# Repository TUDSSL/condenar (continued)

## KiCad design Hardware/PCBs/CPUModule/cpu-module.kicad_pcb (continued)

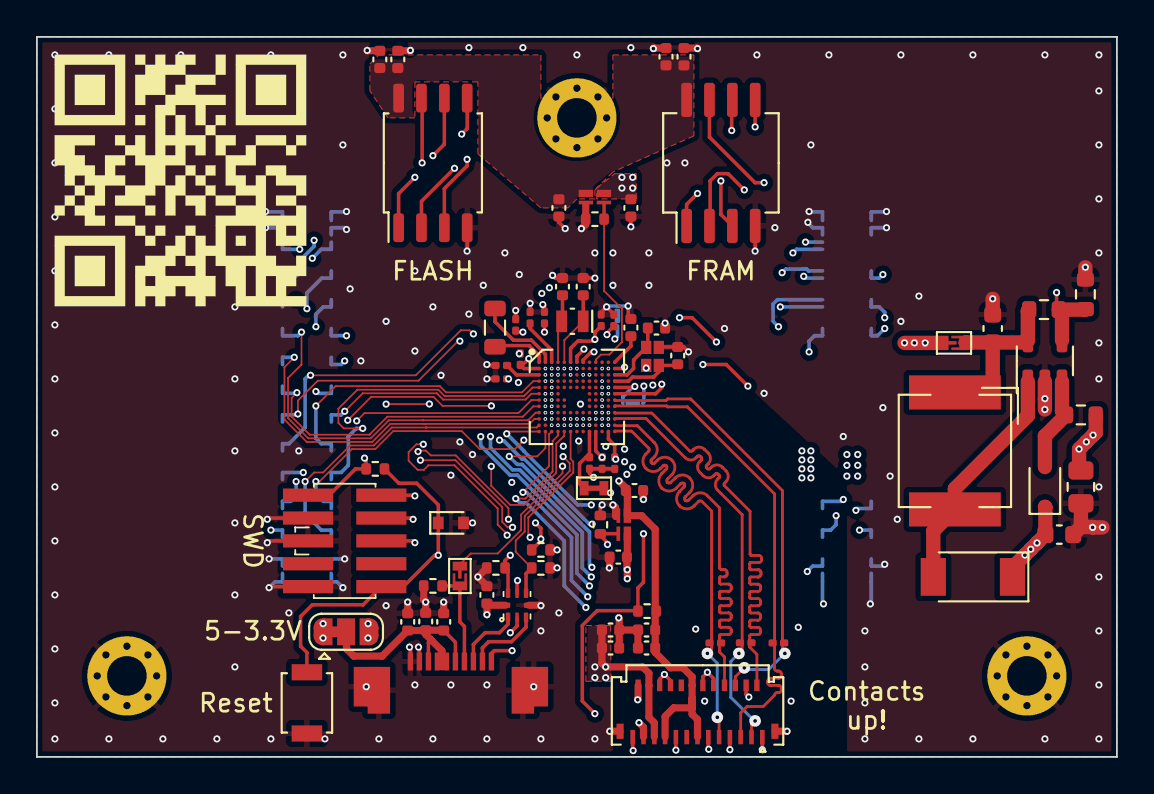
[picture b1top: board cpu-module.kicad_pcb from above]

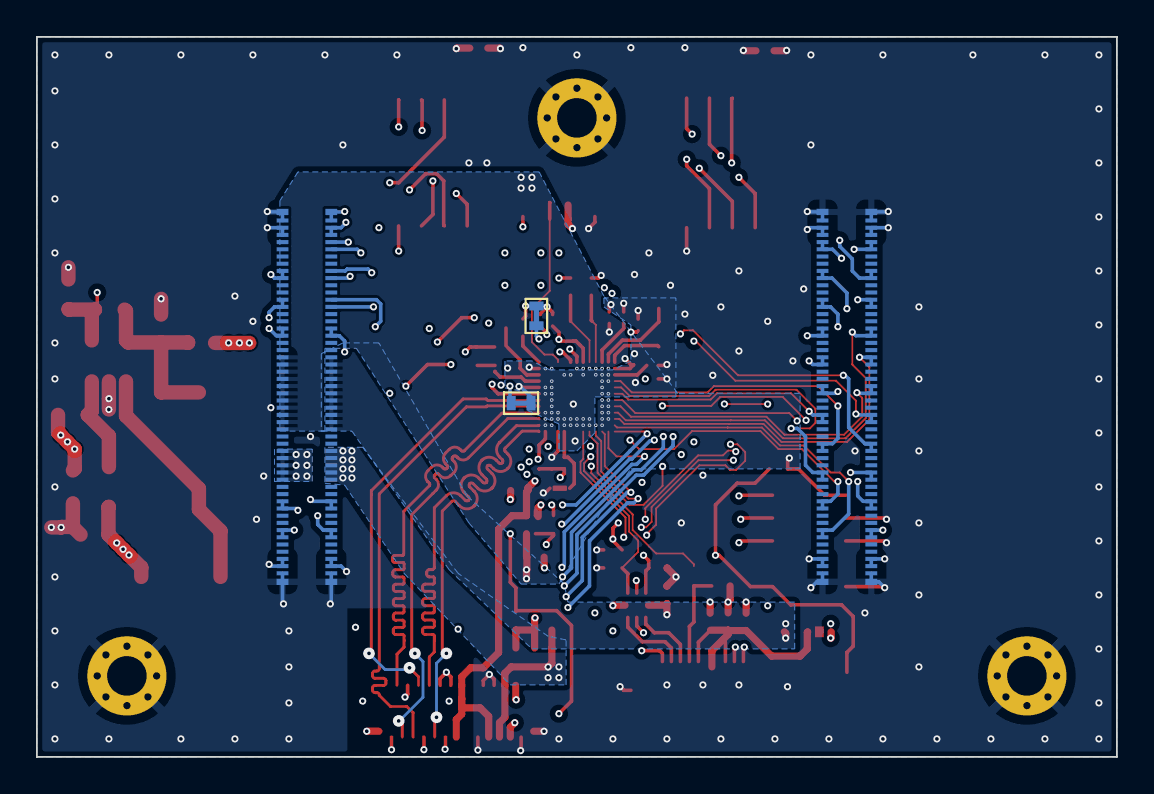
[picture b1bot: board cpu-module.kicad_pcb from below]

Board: 4 copper layers, 60.0 x 40.0 mm, 80 parts (4 on the bottom side), 98 nets.

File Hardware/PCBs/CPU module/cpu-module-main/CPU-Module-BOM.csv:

Item,Qty,Reference(s),Value,LibPart,Footprint,Datasheet,MPN
1,2,"C1, C3",6pF,Device:C,Capacitor_SMD:C_0402_1005Metric,~,CC0402BRNPO9BN6R0
2,6,"C2, C12, C13, C14, C15, C16",2.2 uF,Device:C,Capacitor_SMD:C_0201_0603Metric,~,GRM033R61A225KE47D
3,7,"C4, C18, C19, C23, C29, C32, C33",100nF,Device:C,Capacitor_SMD:C_0402_1005Metric,~,GRM155R71C104KA88J
4,2,"C5, C8",4pF DNP,Device:C,Capacitor_SMD:C_0402_1005Metric,~,CQ0402ARNPO9BN4R0
5,4,"C6, C7, C9, C10",1uF,Device:C,Capacitor_SMD:C_0201_0603Metric,~,GRM033C81A105ME05D
6,1,C11,4.7nF,Device:C,Capacitor_SMD:C_0201_0603Metric,~,GRM033R61E472KA12D
7,9,"C17, C21, C22, C26, C27, C28, C30, C31, C34",1uF,Device:C,Capacitor_SMD:C_0402_1005Metric,~,CL05A105KP5NNNC
8,1,C20,10uF,Device:C,Capacitor_SMD:C_0603_1608Metric,~,GRT188R61C106KE13D
9,1,C24,2.2uF,Device:C,Capacitor_SMD:C_0603_1608Metric,~,GRM188R61H225KE11D
10,1,C25,10uF,Device:C,Capacitor_SMD:C_0402_1005Metric,~,CL05A106MP8NUB8
11,1,D1,ESD,Device:D_Zener,Diode_SMD:D_SOD-523,~,PESD5V0X1UB
12,1,D2,"PMEG4050EP,115",Device:D_Schottky_Filled,Diode_SMD:D_SOD-128,~,"PMEG4050EP,115"
13,1,D3,"BZX84J-C20,115",Device:D_Schottky_Filled,Diode_SMD:D_SOD-323F,~,"BZX84J-C20,115"
14,1,J1,SWD_10,jaspers_lib:SWD_10,jaspers_footprints:ftsh-105-01-f-dv-k,http://infocenter.arm.com/help/topic/com.arm.doc.ddi0314h/DD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,ftsh-105-01-f-dv-k
15,1,J3,52745-1097,jaspers_lib:52745-1097,jaspers_footprints:FPC_10_TOP,~,52745-1097
16,1,J8,FH35C-25S-0.3SHW(50),Connector_Generic_MountingPin:Conn_01x25_MountingPin,jaspers_footprints:FH35C-25S-0.3SHW_2Rows-27Pins-1MP_P0.60mm_Horizontal,~,FH35C-25S-0.3SHW(50)
17,2,"J10, J11",DF40C-100DP-0-4V,jaspers_lib:DF40C-100DP-0-4V,jaspers_footprints:DF40C-100DP,~,DF40C-100DP-0-4V
18,1,L1,2.2 uH,Device:L,Inductor_SMD:L_0805_2012Metric,~,DFE201210U-2R2M=P2
19,1,L2,LQH3NPH150MMEL,Device:L,jaspers_footprints:VLS6045EX,~,LQH3NPH150MMEL
20,3,"R1, R5, R14",100k,Device:R,Resistor_SMD:R_0402_1005Metric,~,ERJ-2RKF1003X
21,3,"R2, R3, R4",100 DNP,Device:R,Resistor_SMD:R_0201_0603Metric,~,CRCW0201100RFNED
22,1,R6,0,Device:R,Resistor_SMD:R_0402_1005Metric,~,ERJ-2GE0R00X
23,1,R7,DNP,Device:R,Resistor_SMD:R_0603_1608Metric,~,
24,4,"R8, R9, R10, R15",10M,Device:R,Resistor_SMD:R_0402_1005Metric,~,RC0402FR-0710ML
25,1,R11,100k,Device:R,Resistor_SMD:R_0603_1608Metric,~,ERJ-3EKF1003V
26,1,R12,100,Device:R,Resistor_SMD:R_0603_1608Metric,~,CRCW0603100RFKEAHP
27,1,R13,ERJP06F10R0V,Device:R,Resistor_SMD:R_0805_2012Metric,~,ERJP06F10R0V
28,1,SW1,SW_Push,Switch:SW_Push,Button_Switch_SMD:SW_SPST_B3U-1000P,~,B3U-1000P
29,1,U1,Apollo_4,jaspers_lib:Apollo_4,jaspers_footprints:Apollo4-BGA-156_13x12_5.0x5.0mm,,Apollo 4
30,2,"U2, U7",SLG5NT1593V,jaspers_lib:SLG5NT1593V,jaspers_footprints:SLG5NT1593V,https://www.mouser.com/datasheet/2/665/silego_04052017_SLG5N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,SLG5NT1593V
31,1,U3,SN74AUP3G34RSE,jaspers_lib:SN74AUP3G34RSE,jaspers_footprints:Texas_RSE_8_UQFN,https://www.ti.com/lit/ds/symlink/sn74aup3g34.pdf,SN74AUP3G34RSE
32,1,U4,LM3410XMF,jaspers_lib:LM3410XMF,Package_TO_SOT_SMD:SOT-23-5,https://www.ti.com/lit/ds/symlink/lm3410.pdf,LM3410XMF
33,1,U5,MX25R6435FM2IH0,jaspers_lib:MX25R6435FM2IH0,Package_SO:SOP-8_5.28x5.23mm_P1.27mm,https://www.farnell.com/datasheets/2815329.pdf,MX25R6435FM2IH0
34,1,U6,MB85RS4MT,jaspers_lib:MB85RS4MT,Package_SO:SO-8_5.3x6.2mm_P1.27mm,https://www.fujitsu.com/global/documents/products/devices/se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,MB85RS4MT
35,1,Y1,32.768Hz,Device:Crystal,Crystal:Crystal_SMD_MicroCrystal_CM9V-T1A-2Pin_1.6x1.0mm,http://www.txccrystal.com/images/pdf/9ht12.pdf,9HT12-32.768KDZY
36,1,Y2,ABM12W-32.0000MHZ,jaspers_lib:ABM12W-32.0000MHZ,jaspers_footprints:Crystal_SMD_Abracon_ABM12B-4Pin_1.6x1.2mm,https://abracon.com/Resonators/ABM12W.pdf,ABM12W-32.0000MHZ-6-D1X-T3

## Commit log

2023-09-01 folder structure created
2023-09-01 cleaning of DS_Store
2023-09-01 removal of remaining .DS_Store files
2023-09-01 readme files added
2023-09-01 new readme files added
2023-09-01 preliminary studies files added
2023-09-03 Preliminary study software and paths shortened
2023-09-03 Enclosure and more paths shortened
2023-09-03 Hardware files
2023-09-03 Update gitignore
2023-09-03 Menu changes and readme
2023-09-03 Change settings readme
2023-09-10 Apply fixes
2023-09-10 Main readme
2023-09-10 Port changes from the preliminary study
2023-09-10 Rename to camelcase
2023-09-25 Log processing
2023-09-25 Add BOMs and more documentation
2023-10-09 Make setting changes
2023-11-21 Current draft final data analysis scripts
2026-01-27 Update ImageSharp package version
    Updated ImageSharp package version from 3.0.0 to 3.1.11.
2026-02-10 Update README.md
    added citation info, related websites and copyright
2026-02-10 Update publication details in README.md
    Updated conference presentation video link and corrected license file reference.
2026-02-10 Create doc-images
    folder for images
2026-02-10 doc-images removed
2026-02-10 Illustration file added and readme revised
2026-02-10 fix url to illustration figure
2026-02-10 fix url to folders
2026-02-10 Rename Data/MainStudy/Data/1_0.csv to Data/MainStudy/Data/Log_Data/1_0.csv
    Added folder for log data
2026-02-10 Log files
    Files for participants 2-10
2026-02-11 Log files
    Log files 11-20
2026-02-11 Log files
    Log files 21-40
2026-02-11 Log files
    Log files 27 and 41-50
2026-02-11 Log files
    Log files 51-60
2026-02-11 Log files
    Log file 1
2026-02-11 System internal components
2026-02-12 NASA-TLX user data
2026-02-12 Complete Survey Data
2026-02-12 Log Data Analysis Scripts
